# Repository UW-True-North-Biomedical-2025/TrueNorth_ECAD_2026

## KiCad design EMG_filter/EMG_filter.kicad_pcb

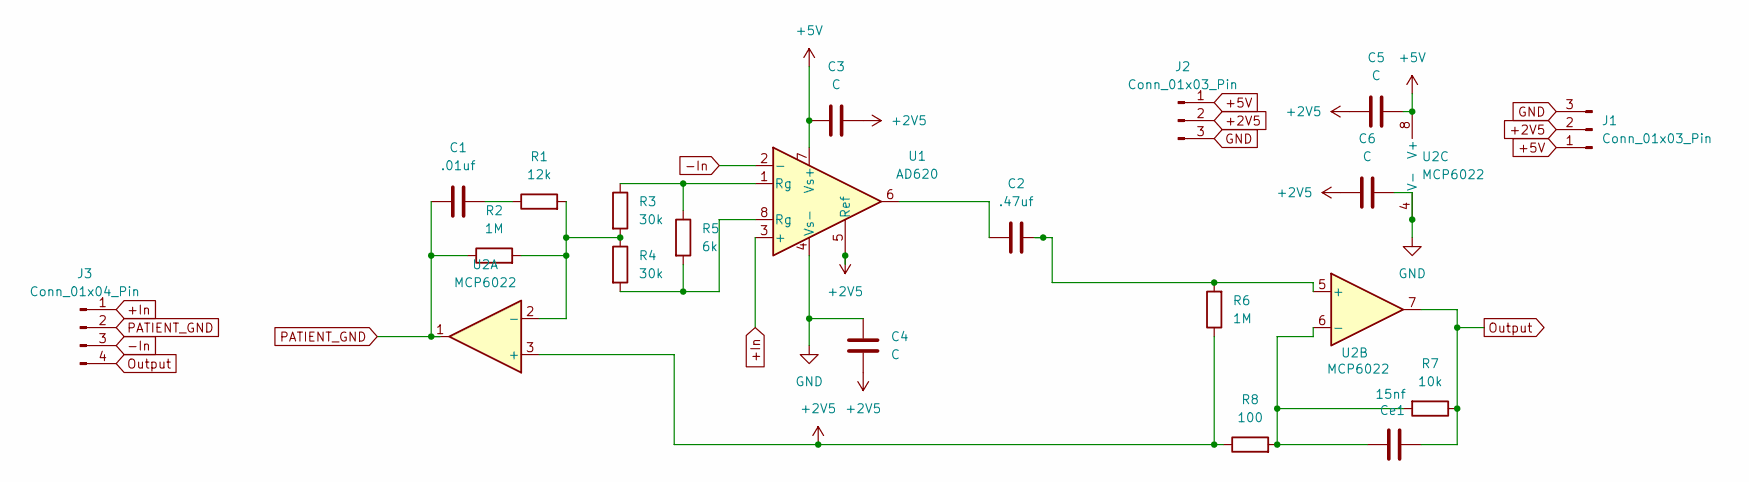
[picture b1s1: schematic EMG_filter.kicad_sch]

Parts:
C1: .01uf; C_0805_2012Metric_Pad1.18x1.45mm_HandSolder
C2: .47uf; C_0805_2012Metric_Pad1.18x1.45mm_HandSolder
C3, C4, C5, C6: C; C_0805_2012Metric_Pad1.18x1.45mm_HandSolder
Ce1: 15nf; C_0805_2012Metric_Pad1.18x1.45mm_HandSolder
J1, J2: Conn_01x03_Pin; CONN_SM03B-SRSS-TB_JST
J3: Conn_01x04_Pin; CONN_SM04B-SRSS-TB_JST
R1: 12k; R_0805_2012Metric_Pad1.20x1.40mm_HandSolder
R2, R6: 1M; R_0805_2012Metric_Pad1.20x1.40mm_HandSolder
R3, R4: 30k; R_0805_2012Metric_Pad1.20x1.40mm_HandSolder
R5: 6k; R_0805_2012Metric_Pad1.20x1.40mm_HandSolder
R7: 10k; R_0805_2012Metric_Pad1.20x1.40mm_HandSolder
R8: 100; R_0805_2012Metric_Pad1.20x1.40mm_HandSolder
U1: AD620; DIP-8_W7.62mm
U2: MCP6022; DIP-8_W7.62mm

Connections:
+2V5: C3.2, C4.1, C5.1, C6.1, J1.2, J2.2, R6.1, R8.1, U1.5 (Ref), U2.3 (+)
+5V: C3.1, C5.2, J1.1, J2.1, U1.7 (Vs+), U2.8 (V+)
+In: J3.1, U1.3 (+)
-In: J3.3, U1.2 (-)
GND: C4.2, C6.2, J1.3, J2.3, U1.4 (Vs-), U2.4 (V-)
unnamed: C1.2, R1.1
unnamed: C2.1, U1.6
unnamed: R3.1, R5.1, U1.1 (Rg)
unnamed: R4.2, R5.2, U1.8 (Rg)
unnamed: R1.2, R2.2, R3.2, R4.1, U2.2 (-)
unnamed: C2.2, R6.2, U2.5 (+)
unnamed: Ce1.2, R7.2, R8.2, U2.6 (-)
Output: Ce1.1, J3.4, R7.1, U2.7
PATIENT_GND: C1.1, J3.2, R2.1, U2.1

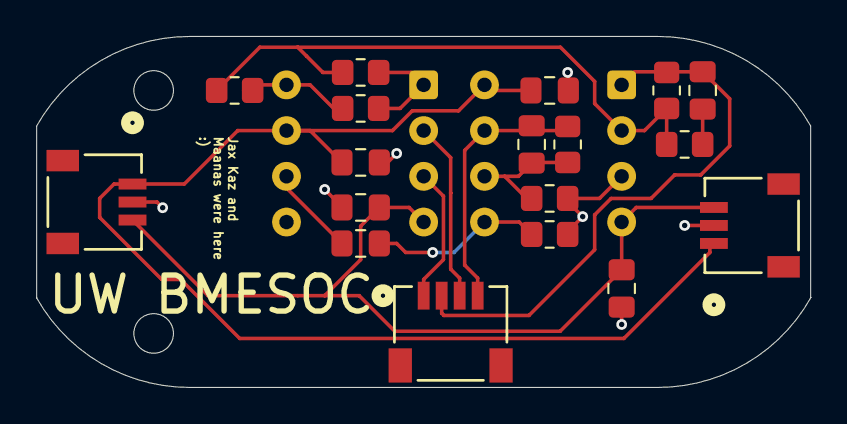
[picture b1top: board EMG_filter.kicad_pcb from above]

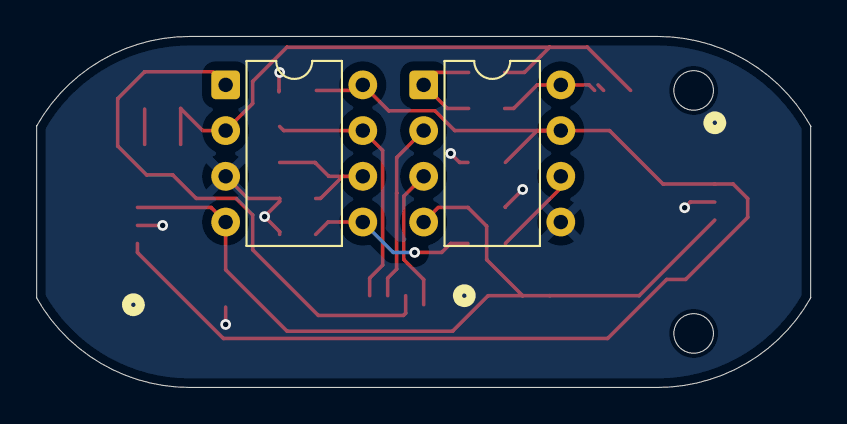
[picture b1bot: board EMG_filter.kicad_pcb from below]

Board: 2 copper layers, 43.0 x 19.5 mm, 20 parts (2 on the bottom side), 14 nets.

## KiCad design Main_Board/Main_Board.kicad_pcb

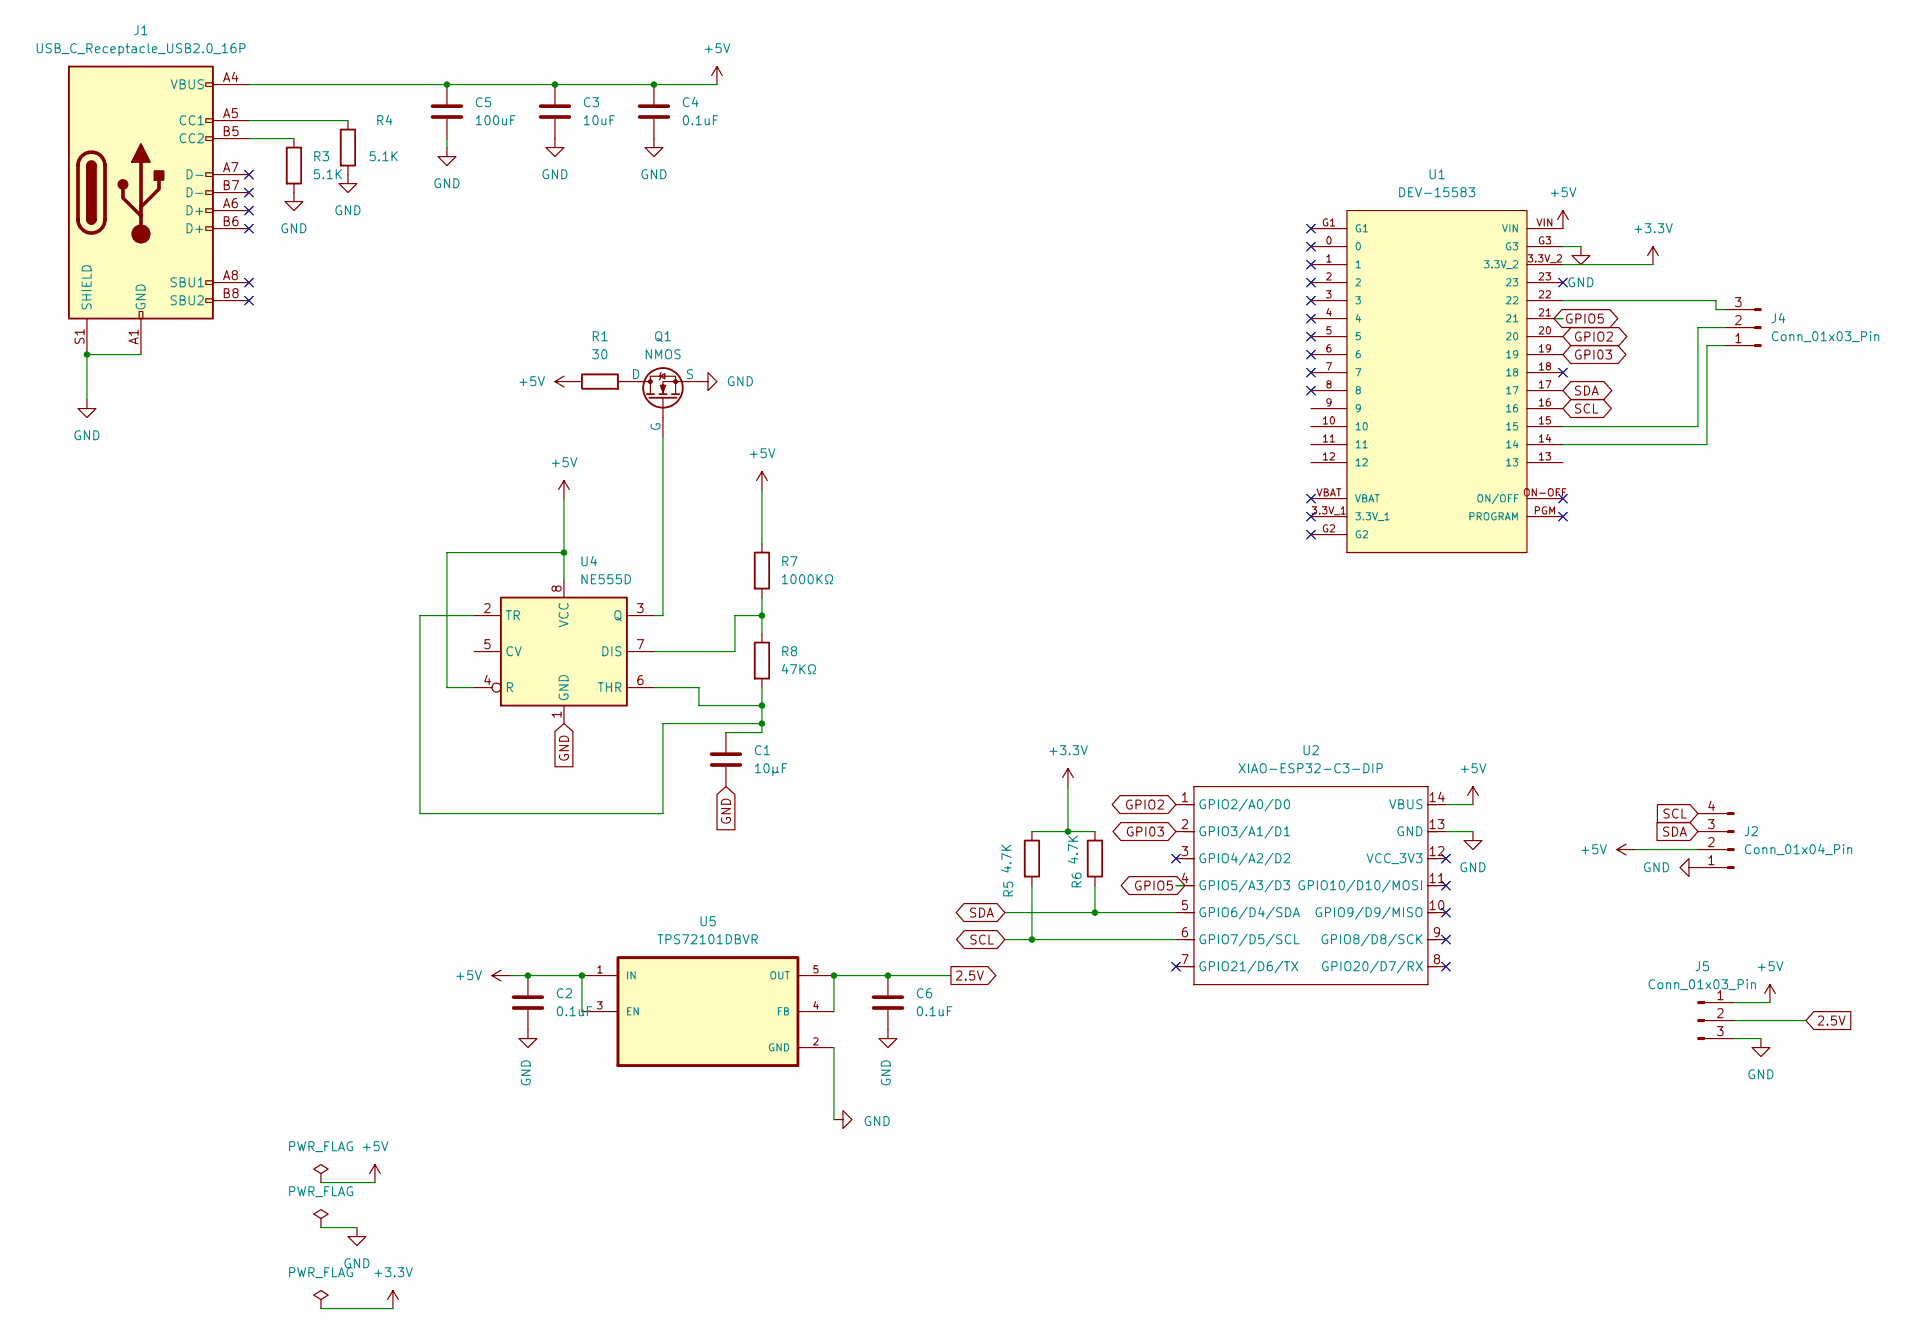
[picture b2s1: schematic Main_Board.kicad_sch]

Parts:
C1: 10μF; C_0805_2012Metric_Pad1.18x1.45mm_HandSolder
C2, C4, C6: 0.1uF; C_0805_2012Metric_Pad1.18x1.45mm_HandSolder
C3: 10uF; C_0805_2012Metric_Pad1.18x1.45mm_HandSolder
C5: 100uF; C_0805_2012Metric_Pad1.18x1.45mm_HandSolder
J1: USB_C_Receptacle_USB2.0_16P; USB_C_Receptacle_HRO_TYPE-C-31-M-12
J2: Conn_01x04_Pin; JST_SH_SM04B-SRSS-TB_1x04-1MP_P1.00mm_Horizontal
J4, J5: Conn_01x03_Pin; JST_SH_SM03B-SRSS-TB_1x03-1MP_P1.00mm_Horizontal
Q1: NMOS; SOT-323_SC-70
R1: 30; R_0805_2012Metric_Pad1.20x1.40mm_HandSolder
R3, R4: 5.1K; R_0805_2012Metric_Pad1.20x1.40mm_HandSolder
R5, R6: 4.7K; R_0805_2012Metric_Pad1.20x1.40mm_HandSolder
R7: 1000KΩ; R_0805_2012Metric_Pad1.20x1.40mm_HandSolder
R8: 47KΩ; R_0805_2012Metric_Pad1.20x1.40mm_HandSolder
U1: DEV-15583; MODULE_DEV-15583
U2: XIAO-ESP32-C3-DIP; MCU_Seeed_ESP32C3
U4: NE555D; SOIC-8_3.9x4.9mm_P1.27mm
U5: TPS72101DBVR; SOT-23-5_HandSoldering; PARTREV MARCH 2006

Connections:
2.5V: C6.1, J5.2, U5.4 (FB), U5.5 (OUT)
+3.3V: R5.1, R6.2, U1.3.3V_2
+5V: C2.1, C3.1, C4.1, C5.1, J1.A4 (VBUS), J1.A9 (VBUS), J1.B4 (VBUS), J1.B9 (VBUS), J2.2, J5.1, R1.1, R7.1, U1.VIN, U2.14 (VBUS), U4.4 (R), U4.8 (VCC), U5.1 (IN), U5.3 (EN)
GND: C1.2, C2.2, C3.2, C4.2, C5.2, C6.2, J1.A1 (GND), J1.A12 (GND), J1.B1 (GND), J1.B12 (GND), J1.S1 (SHIELD), J2.1, J5.3, Q1.3 (S), R3.2, R4.2, U1.G3, U2.13 (GND), U4.1 (GND), U5.2 (GND)
GPI03: U1.19, U2.2 (GPIO3/A1/D1)
GPIO2: U1.20, U2.1 (GPIO2/A0/D0)
GPIO5: U1.21, U2.4 (GPIO5/A3/D3)
unnamed: J1.A5 (CC1), R4.1
unnamed: J1.B5 (CC2), R3.1
unnamed: J4.1, U1.14
unnamed: J4.2, U1.15
unnamed: J4.3, U1.22
unnamed: Q1.1 (D), R1.2
unnamed: Q1.2 (G), U4.3 (Q)
unnamed: R7.2, R8.1, U4.7 (DIS)
unnamed: C1.1, R8.2, U4.2 (TR), U4.6 (THR)
SCL: J2.4, R5.2, U1.16, U2.6 (GPIO7/D5/SCL)
SDA: J2.3, R6.1, U1.17, U2.5 (GPIO6/D4/SDA)

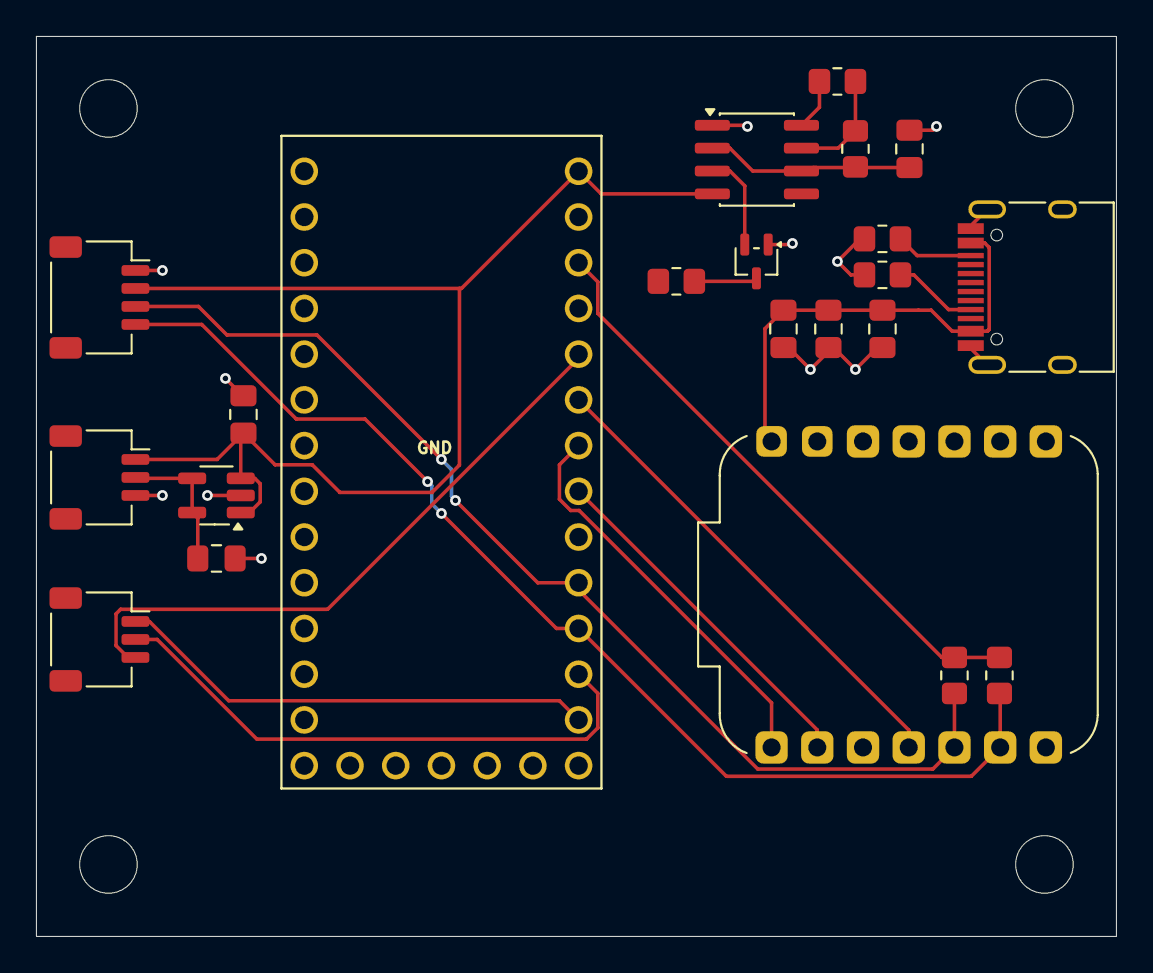
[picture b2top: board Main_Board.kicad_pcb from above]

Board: 2 copper layers, 60.0 x 50.0 mm, 22 parts (0 on the bottom side), 18 nets.

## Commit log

2025-11-26 committed gitignore file
2025-11-26 Initial commit of EMG filter and Main Board KiCad projects
2025-11-26 updated gitignore
2025-11-26 Add greeting to README file
2025-11-27 added teensy symbol and footprint
2025-12-05 added voltage regulator
    added voltage regulator symbol and footprints, placed them on schematic and PCB
2026-01-15 new symbols
2026-01-15 initial PCB
    Played around with some ideas for schematics. board is not finished, but i have a good idea of how the wiring will be managed to avoid crossing lines. need some more consultation to be able to finish
2026-01-21 Adding a LDO regulator symbol AP7375-33SA-7
    added a symbol AP7375-33SA-7 LDO regulator
2026-01-21 First PCB design
    Circuit just needs to be connected with input output and power
2026-01-21 Update EMG_filter.kicad_pcb
    moved it so it dosent collide with border
2026-01-23 minimized pcb
2026-01-28 new footprints for headers
2026-01-28 Teensy Part
    Teensy part with Global Variables and also added hierarchical sheets
2026-01-28 connected vin global variable
2026-01-28 Full power input
    clean power supply, though it hasn't been updated to connect with the esp
2026-01-28 Fixed teensy?
2026-01-28 deleted ADC global labels
2026-01-28 Remodeled PCB to have i/o
2026-01-29 Main board
    The schematic is done, tho I have some concerns...
2026-02-04 updated main PCB
    same thing
2026-02-04 organized
2026-02-04 new filter
2026-02-05 added decoupling caps, bit of rerouting
2026-02-05 added mounting holes
2026-02-05 ground plane covers whole board
2026-02-06 tag
    reviewed and added signatures
2026-02-11 added 555 timer
2026-02-11 changes to main board
2026-02-11 jst sh
2026-02-12 Updated Main board
    not done yet but putting here
2026-02-15 replaced opamp with LDO, completed layout
2026-02-18 moved mounting holes
2026-02-18 updated gitignore to ignore autosaved files
2026-02-18 cleaned up repo
